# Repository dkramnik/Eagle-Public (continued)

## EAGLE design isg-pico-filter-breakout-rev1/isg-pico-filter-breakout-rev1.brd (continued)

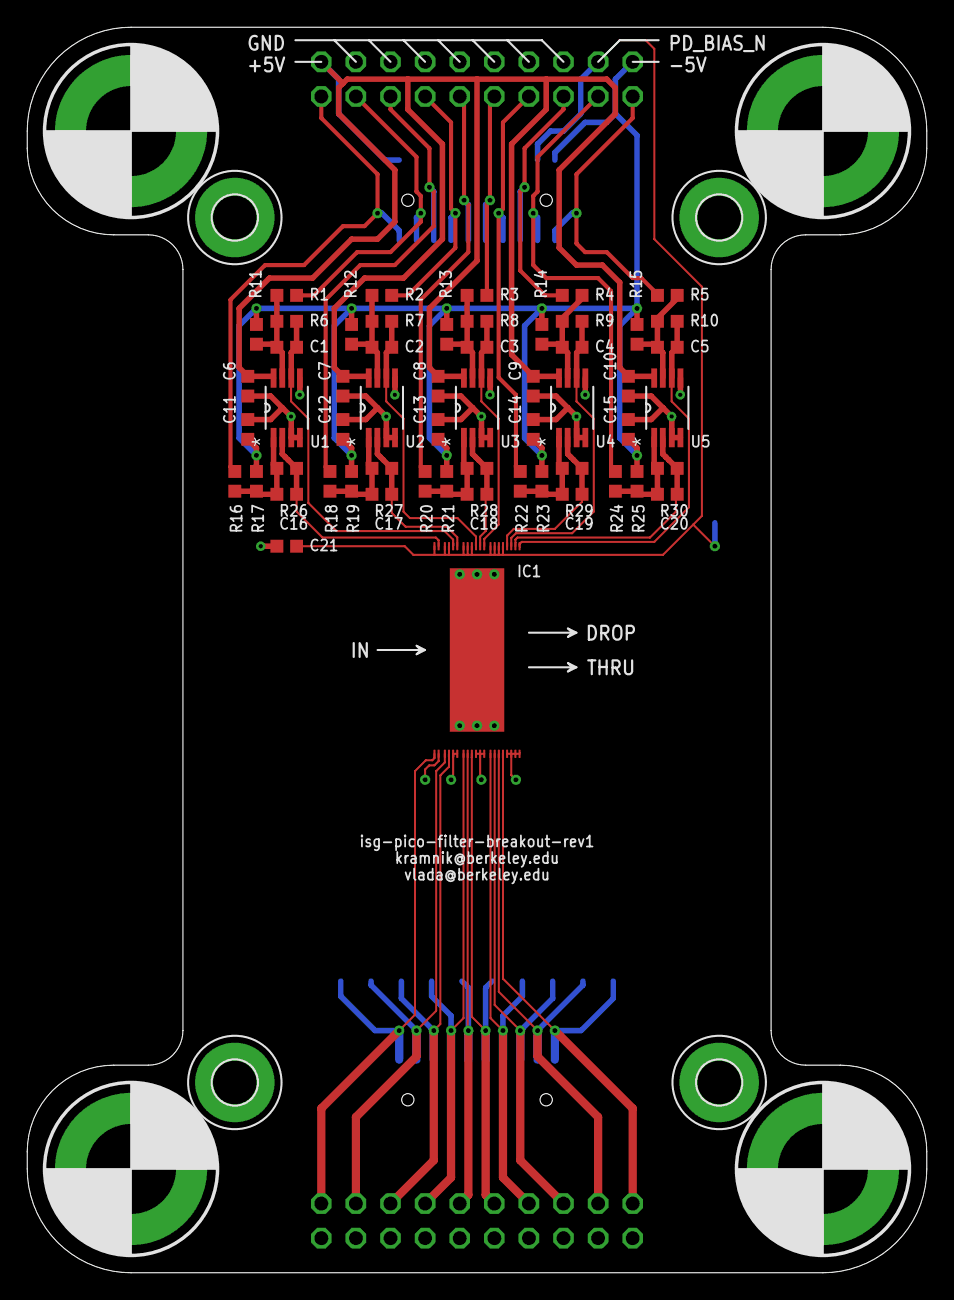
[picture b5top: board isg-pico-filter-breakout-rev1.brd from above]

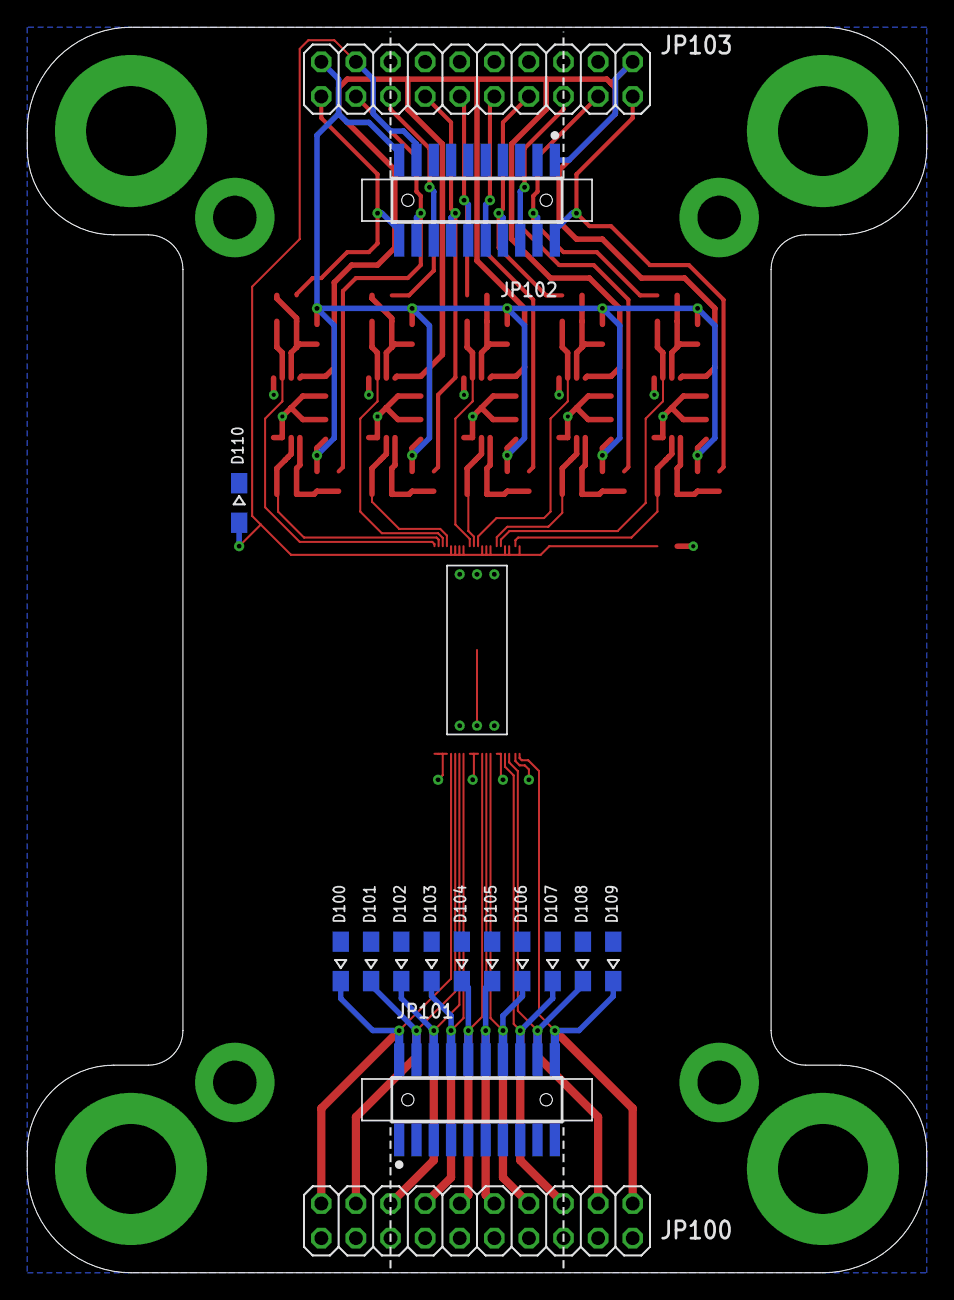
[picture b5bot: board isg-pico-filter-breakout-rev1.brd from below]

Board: 2 copper layers, 66.0 x 91.4 mm, 80 parts (15 on the bottom side), 44 nets.

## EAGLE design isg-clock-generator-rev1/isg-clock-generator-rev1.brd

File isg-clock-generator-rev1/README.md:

<h1>ISG Clock Generator Instructions:</h1>

This board is based off of the TI LMK03318EVM. Refer to the datasheet (http://www.ti.com/lit/ug/snau186/snau186.pdf) for detailed documentation and configuration instructions.

The LMK03318 has 4 on-chip memories: ROM, register file, SRAM, and EEPROM. The currently-used settings are stored in the register file, which is loaded either from ROM or EEPROM on startup, depending on the jumper configuration. The I2C interface writes only to the register file, which can then be transferred to the SRAM. The purpose of the (volatile) SRAM is to store data before it is written to EEPROM. The EEPROM can only be programmed from the contents of the SRAM. The various memory programming steps are separate actions with buttons located all over the TICS GUI, and multiple user actions need to be taken to successfully program the device. The TICS GUI also seems to be buggy, so be patient because it can take several attempts to get the PLL chip to output anything.

Important note: the on-chip EEPROM can only be reprogrammed 100 times, so be conservative when reconfiguring the clock source.

<h2>Required Rework</h2>

If assembled as specified in the BOM, the output coupling networks on channel 2 (the one with differential output) need to be reconfigured to work with the usual ISG CML2CMOS clock receiver design. Instead of DC coupling, each line should be AC-coupled and biased at around 0.8V. The required component changes are:

C34, C35 (AC-coupling) change from 0R 0402 jumper to 1nF 0402 RF capacitor
R22, R24 (pulldown to GND) change from DNP to 800R 0402
R23, R25 (pullup to VDDIO=1.8V) change from DNP to 1k 0402

Location of channel 2's output coupling network:

<h2>Jumper Configuration</h2>

Configure the jumpers like in the picture. STAT1 is on and STAT0 is off when the chip is working as desired.

<h2>Standard EEPROM Configuration Using TICS</h2>

todo

<h2>Custom EEPROM Configuration Using TICS</h2>

Step 1:

Before powering the PLL board, configure the jumpers and connect the TI USB2ANY adapter using the 10-pin ribbon cable.

Step 2:

Plug the TI USB2ANY in to the computer with a USB cable and launch the TICS Pro software. Make sure the adapter connects successfully. When first using the adapter, you will need to follow the on-screen instructions to update the firmware. To select the correct PLL chip, click "Select Device -> Clock Generator/Jitter Cleaner (Single Loop) -> LMK03318" in the main menu bar.

Step 3:

Power the PLL board using a 5V power supply. Hit the "Scan I2C Bus" button on the top-left side of the TICS Pro screen. If the PLL board is powered and connected correctly, the terminal in the bottom-left side of the screen will print: "A device responded at [addr]. Address will be updated."

Step 4:

Use pull-down menus under "Outputs" to configure the output driver type. Note that the configuration bits are written as soon as the menu item is clicked, you do not need to select the new settings and then separately hit a buttom to write to the PLL.

Step 5:

Go to "Wizard" and enter the desired frequencies on each output channel, then hit "Calculate" to populate the tables on the right side. With the tables populated, you can highlight one of the solutions and hit "Use Selected Sol" to program the PLL.

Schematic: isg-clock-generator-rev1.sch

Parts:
C1, C3, C10, C48: DNP; C0603
C2, C39, C41, C50, C52: CAP CER 0.1UF 25V X7R 0603 10%; C0603
C4, C11, C12, C18, C20, C23, C24, C26, C30, C36, C37: CAP CER 0.01uF X7R 0402; C0402
C5, C6, C8, C9, C14, C15, C16, C17, C19, C21, C22, C25, C27, C28, C29, C31, C32, C33, C38, C43, C44, C45, C47: CAP CER 0.1uF X7R 0402; C0402
C7, C46: 0R JUMPER 0603; C0603
C13, C34, C35: 0R JUMPER 0402; C0402
C40, C42: CAP CER 4.7UF 6.3V X5R 0603 10%; C0603
C49, C51: CAP CER 10000PF 25V X7R 0603 10%; C0603
C53: CAP CER 3300pF X7R 0603; C0603
C54: CAP CER 0.033uF X7R 0603; C0603
C55: CAP CER 22uF 6.3V 0603; C0603
C56, C57: CAP CER 1UF 10V X7R 0603 10%; C0603
C100, C101, C102, C103, C104, C105, C106, C107, C108, C109, C110, C111, C112: CAP CER 10uF 6.3V X5R 0603; C0603
D1, D2: SL23HE3_A/I; SMB
H1, H2, H3, H4: MOUNT-PAD-ROUND3.2; 3,2-PAD
IC1: LMK03318RHSR; RHS0048A_NV
IC2, IC3: TPS7A8001DRBR; DRB8_1P75X1P5
JP1: TI_USB2ANY; CON_OST_302-S101
JP2: STAT_LED_EN; JP1
JP3: GPIO0; JP2_ROUND
JP4: HWCTRL; JP2_ROUND
JP5: REFSEL; JP2_ROUND
JP6: EOS_MOTHERBOARD; JP5Q
JP7: PRIREF_VCM; JP2_ROUND
JP8: LOOP_FILTER; JP3Q
JP9: GPIO1; JP2_ROUND
JP10: GPIO2; JP2_ROUND
JP11: GPIO3; JP2_ROUND
JP12: GPIO4; JP2_ROUND
JP13: GPIO5; JP2_ROUND
JP14: XO_MARGIN; JP8Q
L1, L2, L3, L4, L5, L6, L7, L8, L9, L10: FERRITE BEAD 220 OHM 0402 1LN; R0402
LED1: STAT1=LO; CHIP-LED0805
LED2: STAT0=LO; CHIP-LED0805
Q1: 7M50072001; 3.2X2.5_KX-7
R1, R2: RES SMD 510 OHM 1% 1/10W 0603; R0603
R3, R7, R8, R9, R10, R11, R14, R18, R19, R36, R46, R54: DNP; R0603
R4, R12, R13: RES SMD 10K OHM 1% 1/10W 0603; R0603
R5, R37, R38, R39, R40, R41: RES SMD 1K OHM 1% 1/10W 0603; R0603
R6, R43, R44, R45: RES SMD 13.0K OHM 1% 1/10W 0603; R0603
R15, R16, R22, R23, R24, R25: DNP; R0402
R17, R20, R21: 0R JUMPER 0402; R0402
R26: RES SMD 3.92K OHM 1% 1/10W 0603; R0603
R27, R29, R31, R32, R33, R34, R35: RES SMD 4.99K OHM 1% 1/10W 0603; R0603
R28: RES SMD 1.62K OHM 1% 1/10W 0603; R0603
R30, R42: 0R JUMPER 0603; R0603
R47: RES SMD 0 OHM 1% 1/10W 0603; R0603
R48: RES SMD 2.32K OHM 1% 1/10W 0603; R0603
R49: RES SMD 5.62K OHM 1% 1/10W 0603; R0603
R50: RES SMD 10.5K OHM 1% 1/10W 0603; R0603
R51: RES SMD 18.7K OHM 1% 1/10W 0603; R0603
R52: RES SMD 34.8K OHM 1% 1/10W 0603; R0603
R53: RES SMD 84.5K OHM 1% 1/10W 0603; R0603
X1: OUT0_P; J502-ND-142-0701-881/886
X2: PRIREF_N; J502-ND-142-0701-881/886
X3: OUT2_P; J502-ND-142-0701-881/886
X4: PRIREF_P; J502-ND-142-0701-881/886
X5: OUT2_N; J502-ND-142-0701-881/886
X6: V_IN_EXT; 22-23-2021

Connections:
DECAP_DIG: C102.1, IC1.3 (CAP_DIG)
DECAP_LDO: C110.1, IC1.28 (CAP_LDO)
DECAP_PLL: C111.1, IC1.35 (CAP_PLL)
EXT_VDD: JP1.5, R3.1
GND: C1.2, C2.2, C3.2, C4.2, C5.2, C6.2, C8.2, C9.2, C10.2, C11.2, C12.2, C14.2, C15.2, C16.2, C17.2, C18.2, C19.2, C20.2, C21.2, C22.2, C23.2, C24.2, C25.2, C26.2, C27.2, C28.2, C29.2, C30.2, C31.2, C32.2, C33.2, C36.2, C37.2, C38.2, C39.2, C40.2, C41.2, C42.2, C43.2, C44.2, C45.2, C47.2, C48.2, C49.2, C50.2, C51.2, C52.2, C53.2, C54.2, C55.2, C56.2, C57.2, C100.2, C101.2, C102.2, C103.2, C104.2, C105.2, C106.2, C107.2, C108.2, C109.2, C110.2, C111.2, C112.2, H1.B3,2, H2.B3,2, H3.B3,2, H4.B3,2, IC1.49 (PAD), IC2.4 (GND), IC2.PAD (GND), IC2.PAD1 (GND), IC2.PAD2 (GND), IC2.PAD3 (GND), IC2.PAD4 (GND), IC2.VIA1 (GND), IC2.VIA2 (GND), IC3.4 (GND), IC3.PAD (GND), IC3.PAD1 (GND), IC3.PAD2 (GND), IC3.PAD3 (GND), IC3.PAD4 (GND), IC3.VIA1 (GND), IC3.VIA2 (GND), JP1.6, JP3.1, JP4.1, JP5.1, JP6.3, JP6.4, JP6.6, JP7.1, JP9.1, JP10.1, JP11.1, JP12.1, JP13.1, JP14.1, JP14.3, JP14.5, JP14.7, JP14.9, JP14.11, JP14.13, JP14.15, Q1.2 (GND), Q1.4 (GND), R9.1, R10.1, R16.1, R19.1, R22.1, R24.1, R26.2, R28.2, R33.1, R34.1, R35.1, R36.1, X1.G@1 (2), X1.G@2 (2), X1.G@3 (2), X1.G@4 (2), X2.G@1 (2), X2.G@2 (2), X2.G@3 (2), X2.G@4 (2), X3.G@1 (2), X3.G@2 (2), X3.G@3 (2), X3.G@4 (2), X4.G@1 (2), X4.G@2 (2), X4.G@3 (2), X4.G@4 (2), X5.G@1 (2), X5.G@2 (2), X5.G@3 (2), X5.G@4 (2), X6.1
GPIO0/SYNC: IC1.12 (GPIO0), JP1.1, R6.2
GPIO0_JUMPER: JP3.2, R6.1
GPIO1: IC1.24 (GPIO1), R33.2, R37.2, R43.1
GPIO1_JUMPER: JP9.2, R37.1
GPIO2: IC1.30 (GPIO2), R34.2, R38.2, R44.1
GPIO2_JUMPER: JP10.2, R38.1
GPIO3: IC1.31 (GPIO3), R35.2, R39.2, R45.1
GPIO3_JUMPER: JP11.2, R39.1
GPIO4: IC1.32 (GPIO4), R36.2, R40.2, R46.1
GPIO4_JUMPER: JP12.2, R40.1
GPIO5: IC1.33 (GPIO5), R42.1
GPIO5_JUMPER: JP13.2, R42.2, R47.1, R48.1, R49.1, R50.1, R51.1, R52.1, R53.1, R54.1
GPIO5_SEL_1_2: JP14.2, R47.2
GPIO5_SEL_3_4: JP14.4, R48.2
GPIO5_SEL_5_6: JP14.6, R49.2
GPIO5_SEL_7_8: JP14.8, R50.2
GPIO5_SEL_9_10: JP14.10, R51.2
GPIO5_SEL_11_12: JP14.12, R52.2
GPIO5_SEL_13_14: JP14.14, R53.2
GPIO5_SEL_15_16: JP14.16, R54.2
HWCTRL_JUMPER: JP4.2, R4.1
HW_SW_CTRL: IC1.9 (HW_SW_CTRL), JP1.3, JP6.8, R4.2, R7.1, R9.2
LDO_PVCORE_EN: IC3.5 (EN), R32.2
LDO_PVCORE_FB: IC3.3 (FB/SNS), R28.1, R29.1
LDO_PVCORE_SS: C51.1, IC3.6 (NR/SS)
LDO_PVDDIO_EN: IC2.5 (EN), R31.2
LDO_PVDDIO_FB: IC2.3 (FB/SNS), R26.1, R27.1
LDO_PVDDIO_SS: C49.1, IC2.6 (NR/SS)
LF1: C48.1, IC1.34 (LF), R30.1
LF_FRAC_N: C54.1, JP8.3
LF_INT_N\: C53.1, JP8.1
LF_NARROW: C55.1, JP8.5
LF_R: JP8.2, JP8.4, JP8.6, R30.2
unnamed: LED1.A, R1.1
unnamed: LED2.A, R2.1
NC_OUT0_N: IC1.15 (OUT0_N)
NC_OUT1_N: IC1.16 (OUT1_N)
NC_OUT1_P: IC1.17 (OUT1_P)
NC_OUT3_N: IC1.22 (OUT3_N)
NC_OUT3_P: IC1.23 (OUT3_P)
NC_OUT4_N: IC1.38 (OUT4_N)
NC_OUT4_P: IC1.39 (OUT4_P)
NC_OUT5_N: IC1.41 (OUT5_N)
NC_OUT5_P: IC1.42 (OUT5_P)
NC_OUT6_N: IC1.44 (OUT6_N)
NC_OUT6_P: IC1.45 (OUT6_P)
NC_OUT7_N: IC1.47 (OUT7_N)
NC_OUT7_P: IC1.48 (OUT7_P)
NC_PIN: IC1.29 (NC)
NC_USB2ANY_CONN_1: JP1.7
NC_USB2ANY_CONN_2: JP1.8
OUT0_P: IC1.14 (OUT0_P), R17.2
OUT0_R_C_P: C13.2, R15.1, R16.2, X1.1
OUT0_R_P: C13.1, R17.1
OUT2_N: IC1.21 (OUT2_N), R21.2
OUT2_P: IC1.20 (OUT2_P), R20.2
OUT2_R_C_N: C35.2, R24.2, R25.1, X5.1
OUT2_R_C_P: C34.2, R22.2, R23.1, X3.1
OUT2_R_N: C35.1, R21.1
OUT2_R_P: C34.1, R20.1
PDN: C4.1, IC1.13 (PDN), JP1.2
PP_P1V8_VDDO: C14.1, C15.1, C19.1, C22.1, C25.1, C29.1, C32.1, C33.1, C39.1, C40.1, C45.1, IC2.1 (OUT_2), IC2.2 (OUT), L3.2, L4.2, L5.2, L6.2, L7.2, L8.2, R15.2, R23.2, R25.2, R27.2
PP_P3V3_PLL_CORE: C2.1, C5.1, C6.1, C41.1, C42.1, C43.1, C47.1, IC3.1 (OUT_2), IC3.2 (OUT), JP2.2, JP3.3, JP4.3, JP5.3, JP9.3, JP10.3, JP11.3, JP12.3, L1.1, L2.1, L9.1, L10.1, R3.2, R7.2, R8.2, R12.2, R13.2, R18.2, R29.2, R31.1, R41.2, R43.2, R44.2, R45.2, R46.2
PRIREF_N: C7.2, IC1.7 (PRIREF_N), R11.2
PRIREF_P: C46.2, IC1.6 (PRIREF_P), R14.2
PRIREF_R_N: C7.1, X2.1
PRIREF_R_P: C46.1, X4.1
PRIREF_VCM: C1.1, JP7.2, R11.1, R14.1
PRIREF_VCM_DIVIDER: JP7.3, R18.1, R19.2
PULLUP_GPIO5: JP13.3, R41.1
REFSEL: IC1.8 (REFSEL), JP1.4, R5.2, R8.1, R10.2
REFSEL_JUMPER: JP5.2, R5.1
SCL: IC1.26 (SCL), JP1.9, JP6.10, R13.1
SDA: IC1.25 (SDA), JP1.10, JP6.9, R12.1
SECREF_N: C10.1, IC1.11 (SECREF_N), Q1.1
SECREF_P: C3.1, IC1.10 (SECREF_P), Q1.3 (2)
STATUS0: IC1.1 (STATUS0), JP6.7, LED2.C
STATUS1: IC1.2 (STATUS1), JP6.5, LED1.C
STATUS_LED_PWR: JP2.1, R1.2, R2.2
VDDO_01: C16.1, C20.1, C104.1, IC1.18 (VDDO_01), L4.1
VDDO_4: C30.1, C31.1, C108.1, IC1.37 (VDDO_4), L8.1
VDDO_5: C26.1, C28.1, C107.1, IC1.40 (VDDO_5), L7.1
VDDO_6: C21.1, C23.1, C105.1, IC1.43 (VDDO_6), L5.1
VDDO_7: C17.1, C18.1, C103.1, IC1.46 (VDDO_7), L3.1
VDDO_23: C24.1, C27.1, C106.1, IC1.19 (VDDO_23), L6.1
VDD_DIG: C9.1, C12.1, C101.1, IC1.4 (VDD_DIG), L2.2
VDD_IN: C8.1, C11.1, C100.1, IC1.5 (VDD_IN), L1.2
VDD_LDO: C36.1, C44.1, C109.1, IC1.27 (VDD_LDO), L10.2
VDD_PLL: C37.1, C38.1, C112.1, IC1.36 (VDD_PLL), L9.2
VIN: C50.1, C52.1, C56.1, C57.1, D1.C, D2.C, IC2.7 (IN_2), IC2.8 (IN), IC3.7 (IN_2), IC3.8 (IN), R32.1
VIN_EXT: D2.A, X6.2
VIN_MLB: D1.A, JP6.1, JP6.2

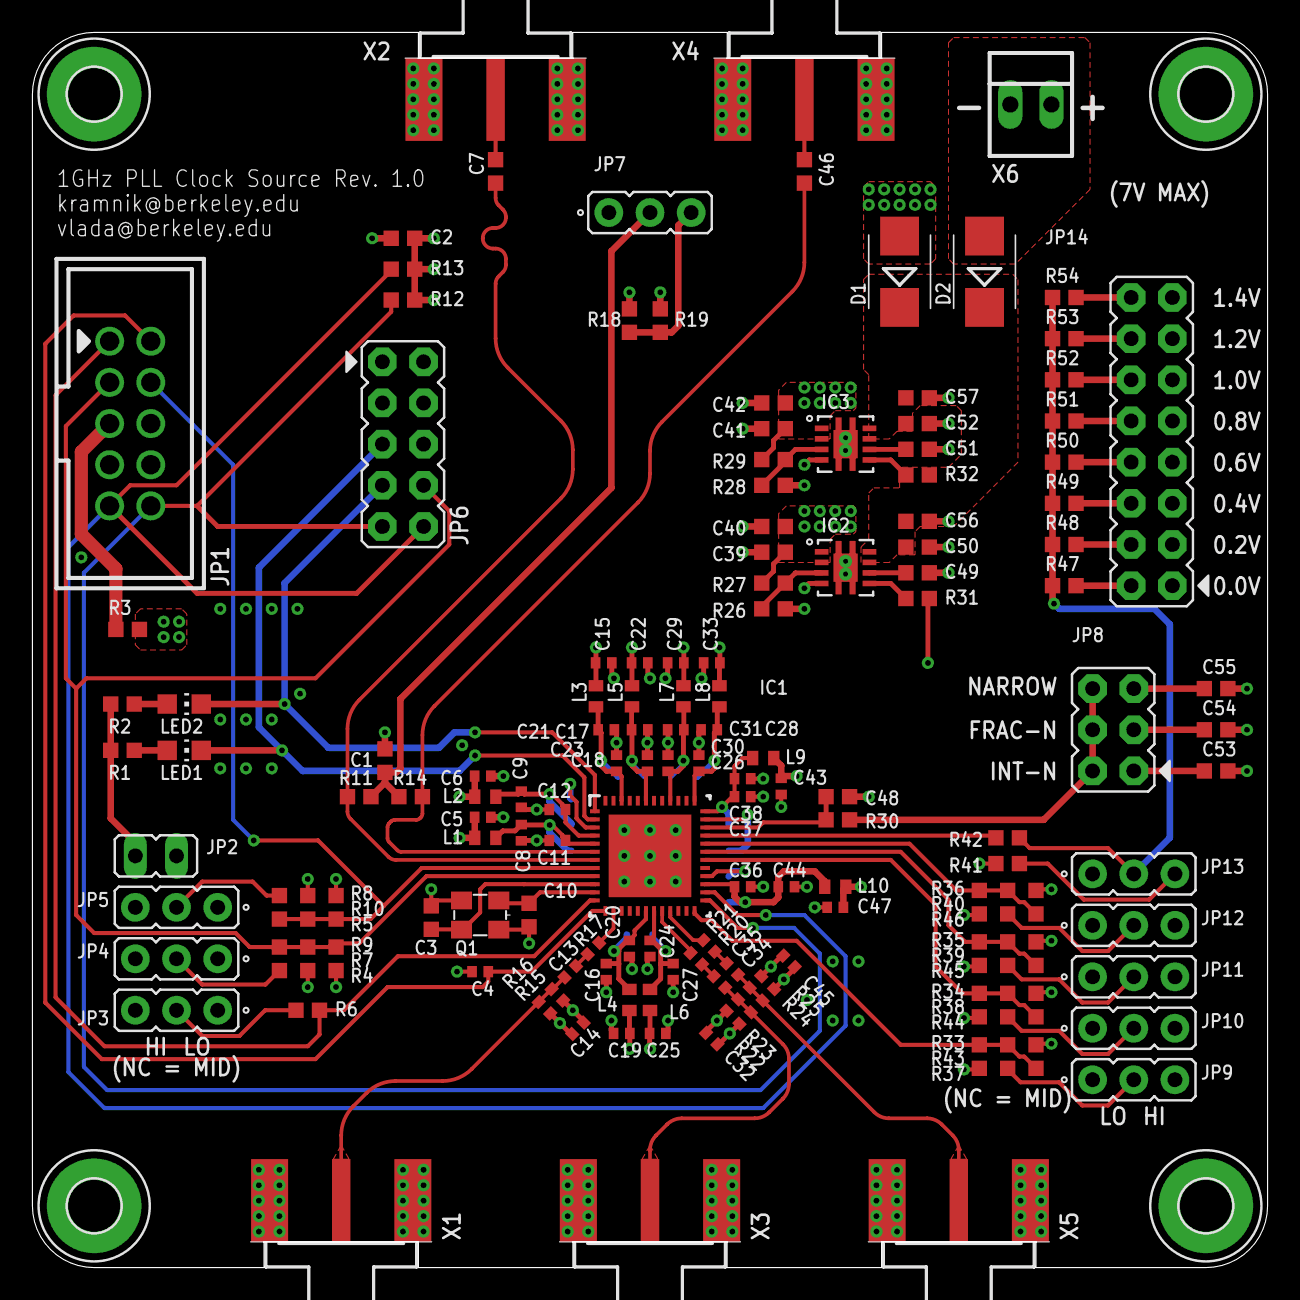
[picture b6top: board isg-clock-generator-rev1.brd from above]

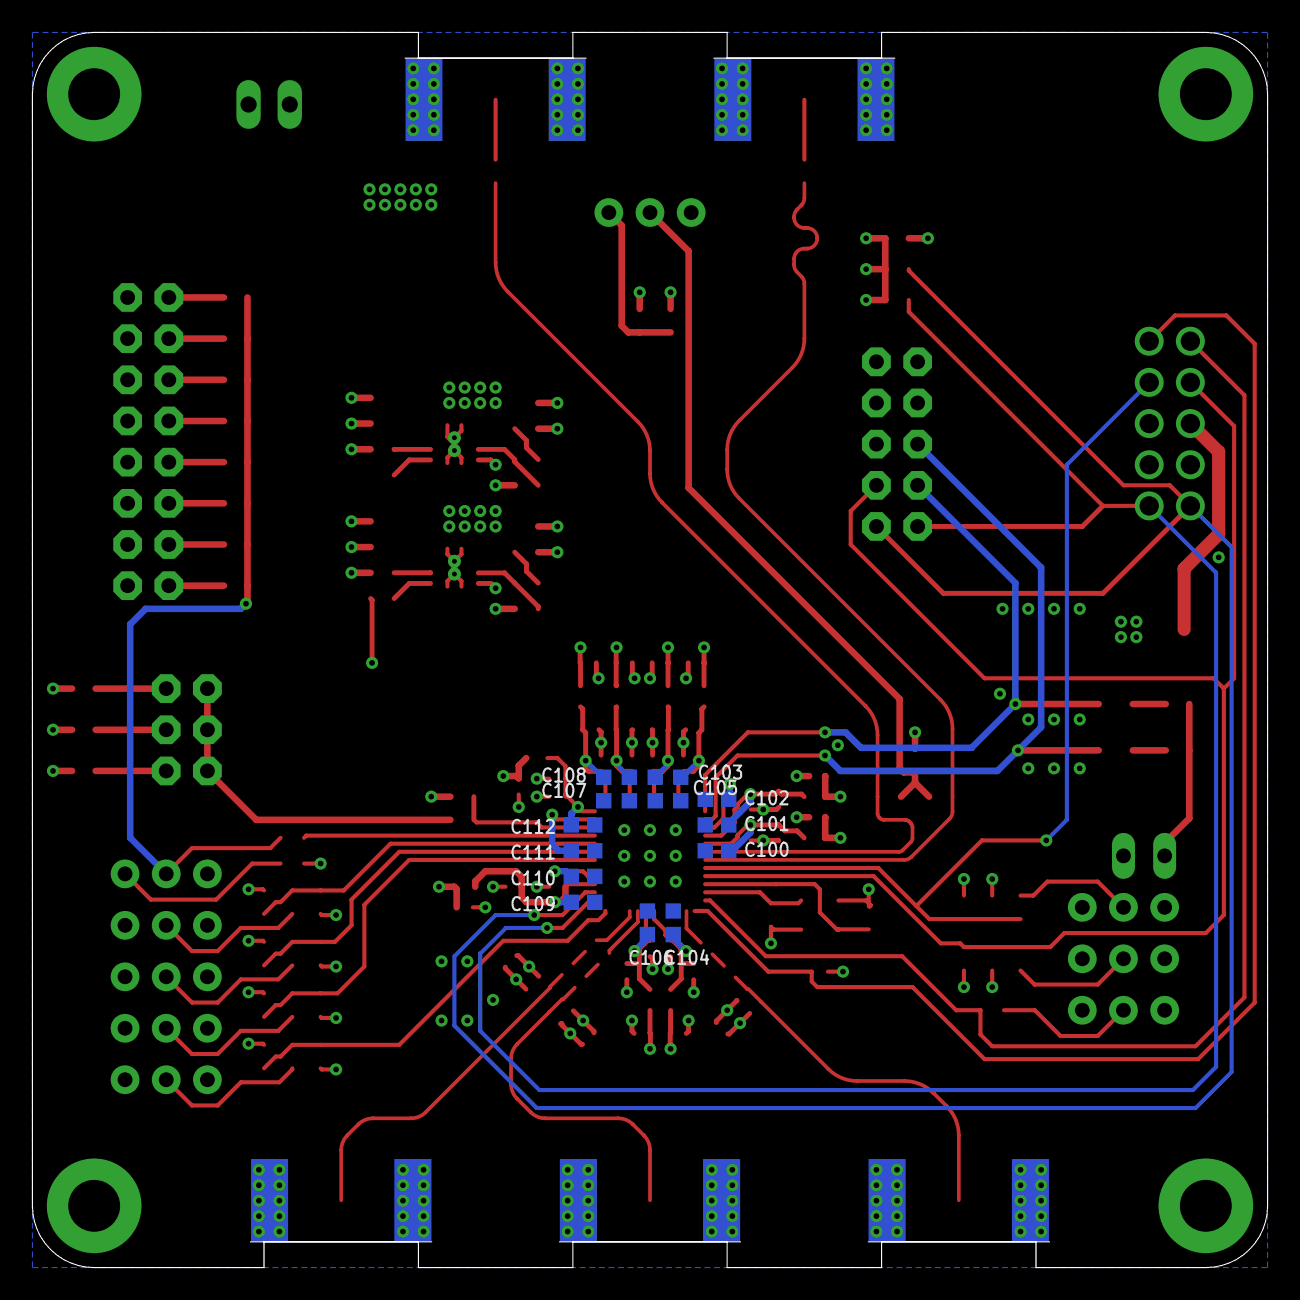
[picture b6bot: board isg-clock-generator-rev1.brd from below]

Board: 4 copper layers, 76.2 x 76.2 mm, 166 parts (13 on the bottom side), 81 nets.

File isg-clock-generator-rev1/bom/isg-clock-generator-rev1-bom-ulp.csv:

"Qty";"Value";"Device";"Package";"Parts";"Description";"MF";"MPN";"OC_FARNELL";"OC_NEWARK";"VALUE";
"2";"0R JUMPER";"C-EUC0603";"C0603";"C7, C46";"CAPACITOR, European symbol";"";"";"";"";"";
"3";"0R JUMPER 0402";"C-EUC0402";"C0402";"C13, C34, C35";"CAPACITOR, European symbol";"";"";"";"";"";
"3";"0R JUMPER 0402";"R-EU_R0402";"R0402";"R17, R20, R21";"RESISTOR, European symbol";"";"";"";"";"";
"2";"0R JUMPER 0603";"R-EU_R0603";"R0603";"R30, R42";"RESISTOR, European symbol";"";"";"";"";"";
"1";"7M50072001";"KX-7";"3.2X2.5_KX-7";"Q1";"Quartz Crystals (MHz) SMD:";"";"";"";"";"";
"11";"CAP CER 0.01uF X7R 0402";"C-EUC0402";"C0402";"C4, C11, C12, C18, C20, C23, C24, C26, C30, C36, C37";"CAPACITOR, European symbol";"";"";"";"";"";
"1";"CAP CER 0.033uF 0603";"C-EUC0603";"C0603";"C54";"CAPACITOR, European symbol";"";"";"";"";"";
"5";"CAP CER 0.1UF 25V X7R 0603 10%";"C-EUC0603";"C0603";"C2, C39, C41, C50, C52";"CAPACITOR, European symbol";"";"";"";"";"";
"23";"CAP CER 0.1uF X7R 0402";"C-EUC0402";"C0402";"C5, C6, C8, C9, C14, C15, C16, C17, C19, C21, C22, C25, C27, C28, C29, C31, C32, C33, C38, C43, C44, C45, C47";"CAPACITOR, European symbol";"";"";"";"";"";
"2";"CAP CER 10000PF 25V X7R 0603 10%";"C-EUC0603";"C0603";"C49, C51";"CAPACITOR, European symbol";"";"";"";"";"";
"13";"CAP CER 10uF 6.3V X5R 0603";"C-EUC0603";"C0603";"C100, C101, C102, C103, C104, C105, C106, C107, C108, C109, C110, C111, C112";"CAPACITOR, European symbol";"";"";"";"";"";
"1";"CAP CER 22uF 6.3V 0603";"C-EUC0603";"C0603";"C55";"CAPACITOR, European symbol";"";"";"";"";"";
"1";"CAP CER 3300pF 0603";"C-EUC0603";"C0603";"C53";"CAPACITOR, European symbol";"";"";"";"";"";
"2";"CAP CER 4.7UF 6.3V X5R 0603 10%";"C-EUC0603";"C0603";"C40, C42";"CAPACITOR, European symbol";"";"";"";"";"";
"3";"DNP";"C-EUC0603";"C0603";"C3, C10, C48";"CAPACITOR, European symbol";"";"";"";"";"";
"6";"DNP";"R-EU_R0402";"R0402";"R15, R16, R22, R23, R24, R25";"RESISTOR, European symbol";"";"";"";"";"";
"10";"DNP";"R-EU_R0603";"R0603";"R3, R7, R8, R9, R10, R11, R14, R36, R46, R54";"RESISTOR, European symbol";"";"";"";"";"";
"1";"DNP 0603";"C-EUC0603";"C0603";"C1";"CAPACITOR, European symbol";"";"";"";"";"";
"2";"DNP 0603";"R-EU_R0603";"R0603";"R18, R19";"RESISTOR, European symbol";"";"";"";"";"";
"1";"EOS_MOTHERBOARD";"JP5Q";"JP5Q";"JP6";"JUMPER";"";"";"";"";"";
"10";"FERRITE BEAD 220 OHM 0402 1LN";"INDUCTOR0402";"R0402";"L1, L2, L3, L4, L5, L6, L7, L8, L9, L10";"";"";"";"";"";"";
"1";"GPIO0";"JP2E";"JP2_ROUND";"JP3";"JUMPER";"";"";"";"";"";
"1";"GPIO1";"JP2E";"JP2_ROUND";"JP9";"JUMPER";"";"";"";"";"";
"1";"GPIO2";"JP2E";"JP2_ROUND";"JP10";"JUMPER";"";"";"";"";"";
"1";"GPIO3";"JP2E";"JP2_ROUND";"JP11";"JUMPER";"";"";"";"";"";
"1";"GPIO4";"JP2E";"JP2_ROUND";"JP12";"JUMPER";"";"";"";"";"";
"1";"GPIO5";"JP2E";"JP2_ROUND";"JP13";"JUMPER";"";"";"";"";"";
"1";"HWCTRL";"JP2E";"JP2_ROUND";"JP4";"JUMPER";"";"";"";"";"";
"1";"LMK03318RHSR";"LMK03318RHSRRHS0048A_NV";"RHS0048A_NV";"IC1";"";"";"";"";"";"LMK03318RHSR";
"1";"LOOP_FILTER";"JP3Q";"JP3Q";"JP8";"JUMPER";"";"";"";"";"";
"4";"MOUNT-PAD-ROUND3.2";"MOUNT-PAD-ROUND3.2";"3,2-PAD";"H1, H2, H3, H4";"MOUNTING PAD, round";"";"";"";"";"";
"1";"OUT0_P";"SMA-142-0701-881/886";"J502-ND-142-0701-881/886";"X1";"SMA 50 Ohm End Launch Jack Receptacle - Round Contact";"JOHNSON COMPONENTS";"142-0701-881";"1608603";"08B906";"";
"1";"OUT2_N";"SMA-142-0701-881/886";"J502-ND-142-0701-881/886";"X5";"SMA 50 Ohm End Launch Jack Receptacle - Round Contact";"JOHNSON COMPONENTS";"142-0701-881";"1608603";"08B906";"";
"1";"OUT2_P";"SMA-142-0701-881/886";"J502-ND-142-0701-881/886";"X3";"SMA 50 Ohm End Launch Jack Receptacle - Round Contact";"JOHNSON COMPONENTS";"142-0701-881";"1608603";"08B906";"";
"1";"PRIREF_N";"SMA-142-0701-881/886";"J502-ND-142-0701-881/886";"X2";"SMA 50 Ohm End Launch Jack Receptacle - Round Contact";"JOHNSON COMPONENTS";"142-0701-881";"1608603";"08B906";"";
"1";"PRIREF_P";"SMA-142-0701-881/886";"J502-ND-142-0701-881/886";"X4";"SMA 50 Ohm End Launch Jack Receptacle - Round Contact";"JOHNSON COMPONENTS";"142-0701-881";"1608603";"08B906";"";
"1";"PRIREF_VCM";"JP2E";"JP2_ROUND";"JP7";"JUMPER";"";"";"";"";"";
"1";"REFSEL";"JP2E";"JP2_ROUND";"JP5";"JUMPER";"";"";"";"";"";
"1";"RES SMD 0 OHM 1% 1/10W 0603";"R-EU_R0603";"R0603";"R47";"RESISTOR, European symbol";"";"";"";"";"";
"1";"RES SMD 1.62K OHM 1% 1/10W 0603";"R-EU_R0603";"R0603";"R28";"RESISTOR, European symbol";"";"";"";"";"";
"1";"RES SMD 10.5K OHM 1% 1/10W 0603";"R-EU_R0603";"R0603";"R50";"RESISTOR, European symbol";"";"";"";"";"";
"3";"RES SMD 10K OHM 1% 1/10W 0603";"R-EU_R0603";"R0603";"R4, R12, R13";"RESISTOR, European symbol";"";"";"";"";"";
"4";"RES SMD 13.0K OHM 1% 1/10W 0603";"R-EU_R0603";"R0603";"R6, R43, R44, R45";"RESISTOR, European symbol";"";"";"";"";"";
"1";"RES SMD 18.7K OHM 1% 1/10W 0603";"R-EU_R0603";"R0603";"R51";"RESISTOR, European symbol";"";"";"";"";"";
"6";"RES SMD 1K OHM 1% 1/10W 0603";"R-EU_R0603";"R0603";"R5, R37, R38, R39, R40, R41";"RESISTOR, European symbol";"";"";"";"";"";
"1";"RES SMD 2.32K OHM 1% 1/10W 0603";"R-EU_R0603";"R0603";"R48";"RESISTOR, European symbol";"";"";"";"";"";
"1";"RES SMD 3.92K OHM 1% 1/10W 0603";"R-EU_R0603";"R0603";"R26";"RESISTOR, European symbol";"";"";"";"";"";
"1";"RES SMD 34.8K OHM 1% 1/10W 0603";"R-EU_R0603";"R0603";"R52";"RESISTOR, European symbol";"";"";"";"";"";
"7";"RES SMD 4.99K OHM 1% 1/10W 0603";"R-EU_R0603";"R0603";"R27, R29, R31, R32, R33, R34, R35";"RESISTOR, European symbol";"";"";"";"";"";
"1";"RES SMD 5.62K OHM 1% 1/10W 0603";"R-EU_R0603";"R0603";"R49";"RESISTOR, European symbol";"";"";"";"";"";
"2";"RES SMD 510R 0603";"R-EU_R0603";"R0603";"R1, R2";"RESISTOR, European symbol";"";"";"";"";"";
"1";"RES SMD 84.5K OHM 1% 1/10W 0603";"R-EU_R0603";"R0603";"R53";"RESISTOR, European symbol";"";"";"";"";"";
"2";"SL23HE3_A/I";"SCHOTTKY-DIODESMD";"SMB";"D1, D2";"Schottky Diode";"";"";"";"";"";
"1";"STAT0=LO";"LEDCHIP-LED0805";"CHIP-LED0805";"LED2";"LED";"";"";"";"";"";
"1";"STAT1=LO";"LEDCHIP-LED0805";"CHIP-LED0805";"LED1";"LED";"";"";"";"";"";
"1";"STAT_LED_EN";"JP1Q";"JP1";"JP2";"JUMPER";"";"";"";"";"";
"1";"TI_USB2ANY";"CON_OST_302-S101";"CON_OST_302-S101";"JP1";"";"";"";"";"";"";
"2";"TPS7A8001DRBR";"TPS7A8001DRBR";"DRB8_1P75X1P5";"IC2, IC3";"";"";"";"";"";"TPS7A8001DRBR";
"1";"V_IN_EXT";"22-23-2021";"22-23-2021";"X6";".100" (2.54mm) Center Header - 2 Pin";"MOLEX";"22-23-2021";"1462926";"25C3832";"";
"1";"XO_MARGIN";"JP8Q";"JP8Q";"JP14";"JUMPER";"";"";"";"";"";

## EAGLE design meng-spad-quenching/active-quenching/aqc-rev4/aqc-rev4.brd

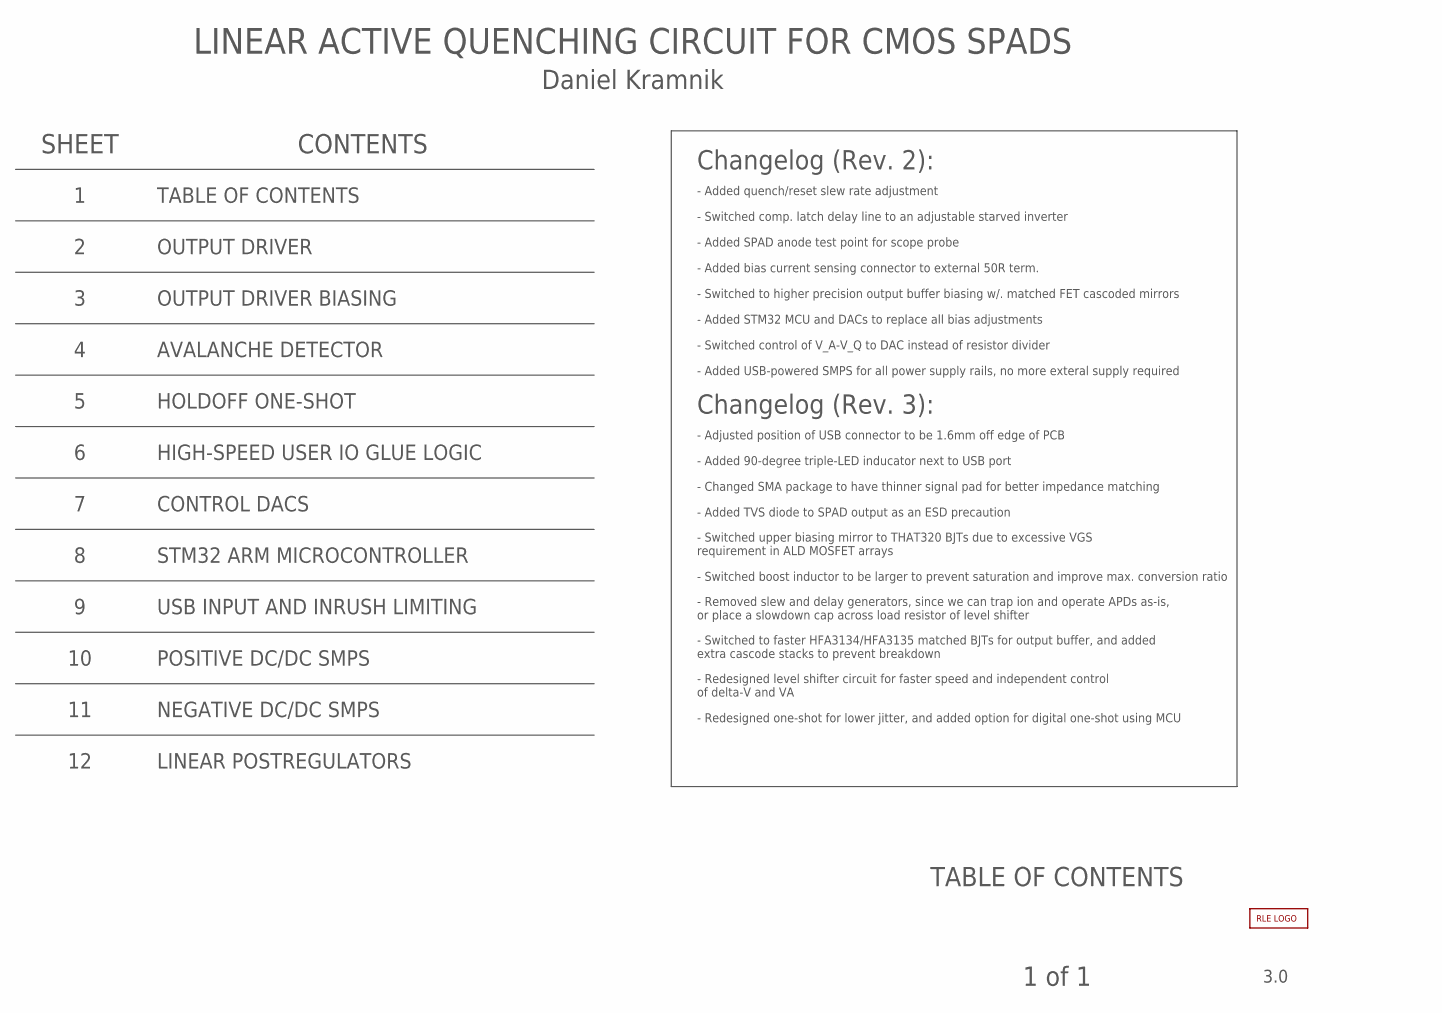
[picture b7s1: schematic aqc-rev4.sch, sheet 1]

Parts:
DNP1000: RLE_LOGO

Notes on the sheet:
Changelog (Rev. 2):
- Added quench/reset slew rate adjustment
- Switched comp. latch delay line to an adjustable starved inverter
- Added SPAD anode test point for scope probe
- Added bias current sensing connector to external 50R term.
- Added USB-powered SMPS for all power supply rails, no more exteral supply required
- Added STM32 MCU and DACs to replace all bias adjustments
- Switched to higher precision output buffer biasing w/. matched FET cascoded mirrors
- Switched control of V_A-V_Q to DAC instead of resistor divider
TABLE OF CONTENTS
3.0
1 of 1
LINEAR ACTIVE QUENCHING CIRCUIT FOR CMOS SPADS
SHEET
CONTENTS
Daniel Kramnik
OUTPUT DRIVER
OUTPUT DRIVER BIASING
STM32 ARM MICROCONTROLLER
CONTROL DACS
AVALANCHE DETECTOR
POSITIVE DC/DC SMPS
NEGATIVE DC/DC SMPS
USB INPUT AND INRUSH LIMITING
HOLDOFF ONE-SHOT
LINEAR POSTREGULATORS
Changelog (Rev. 3):
- Adjusted position of USB connector to be 1.6mm off edge of PCB
- Added 90-degree triple-LED inducator next to USB port
- Changed SMA package to have thinner signal pad for better impedance matching
- Added TVS diode to SPAD output as an ESD precaution
- Switched upper biasing mirror to THAT320 BJTs due to excessive VGS requirement in ALD MOSFET arrays
- Switched boost inductor to be larger to prevent saturation and improve max. conversion ratio
- Removed slew and delay generators, since we can trap ion and operate APDs as-is, or place a slowdown cap across load resistor of level shifter
- Switched to faster HFA3134/HFA3135 matched BJTs for output buffer, and added extra cascode stacks to prevent breakdown
- Redesigned level shifter circuit for faster speed and independent control of delta-V and VA
- Redesigned one-shot for lower jitter, and added option for digital one-shot using MCU
HIGH-SPEED USER IO GLUE LOGIC

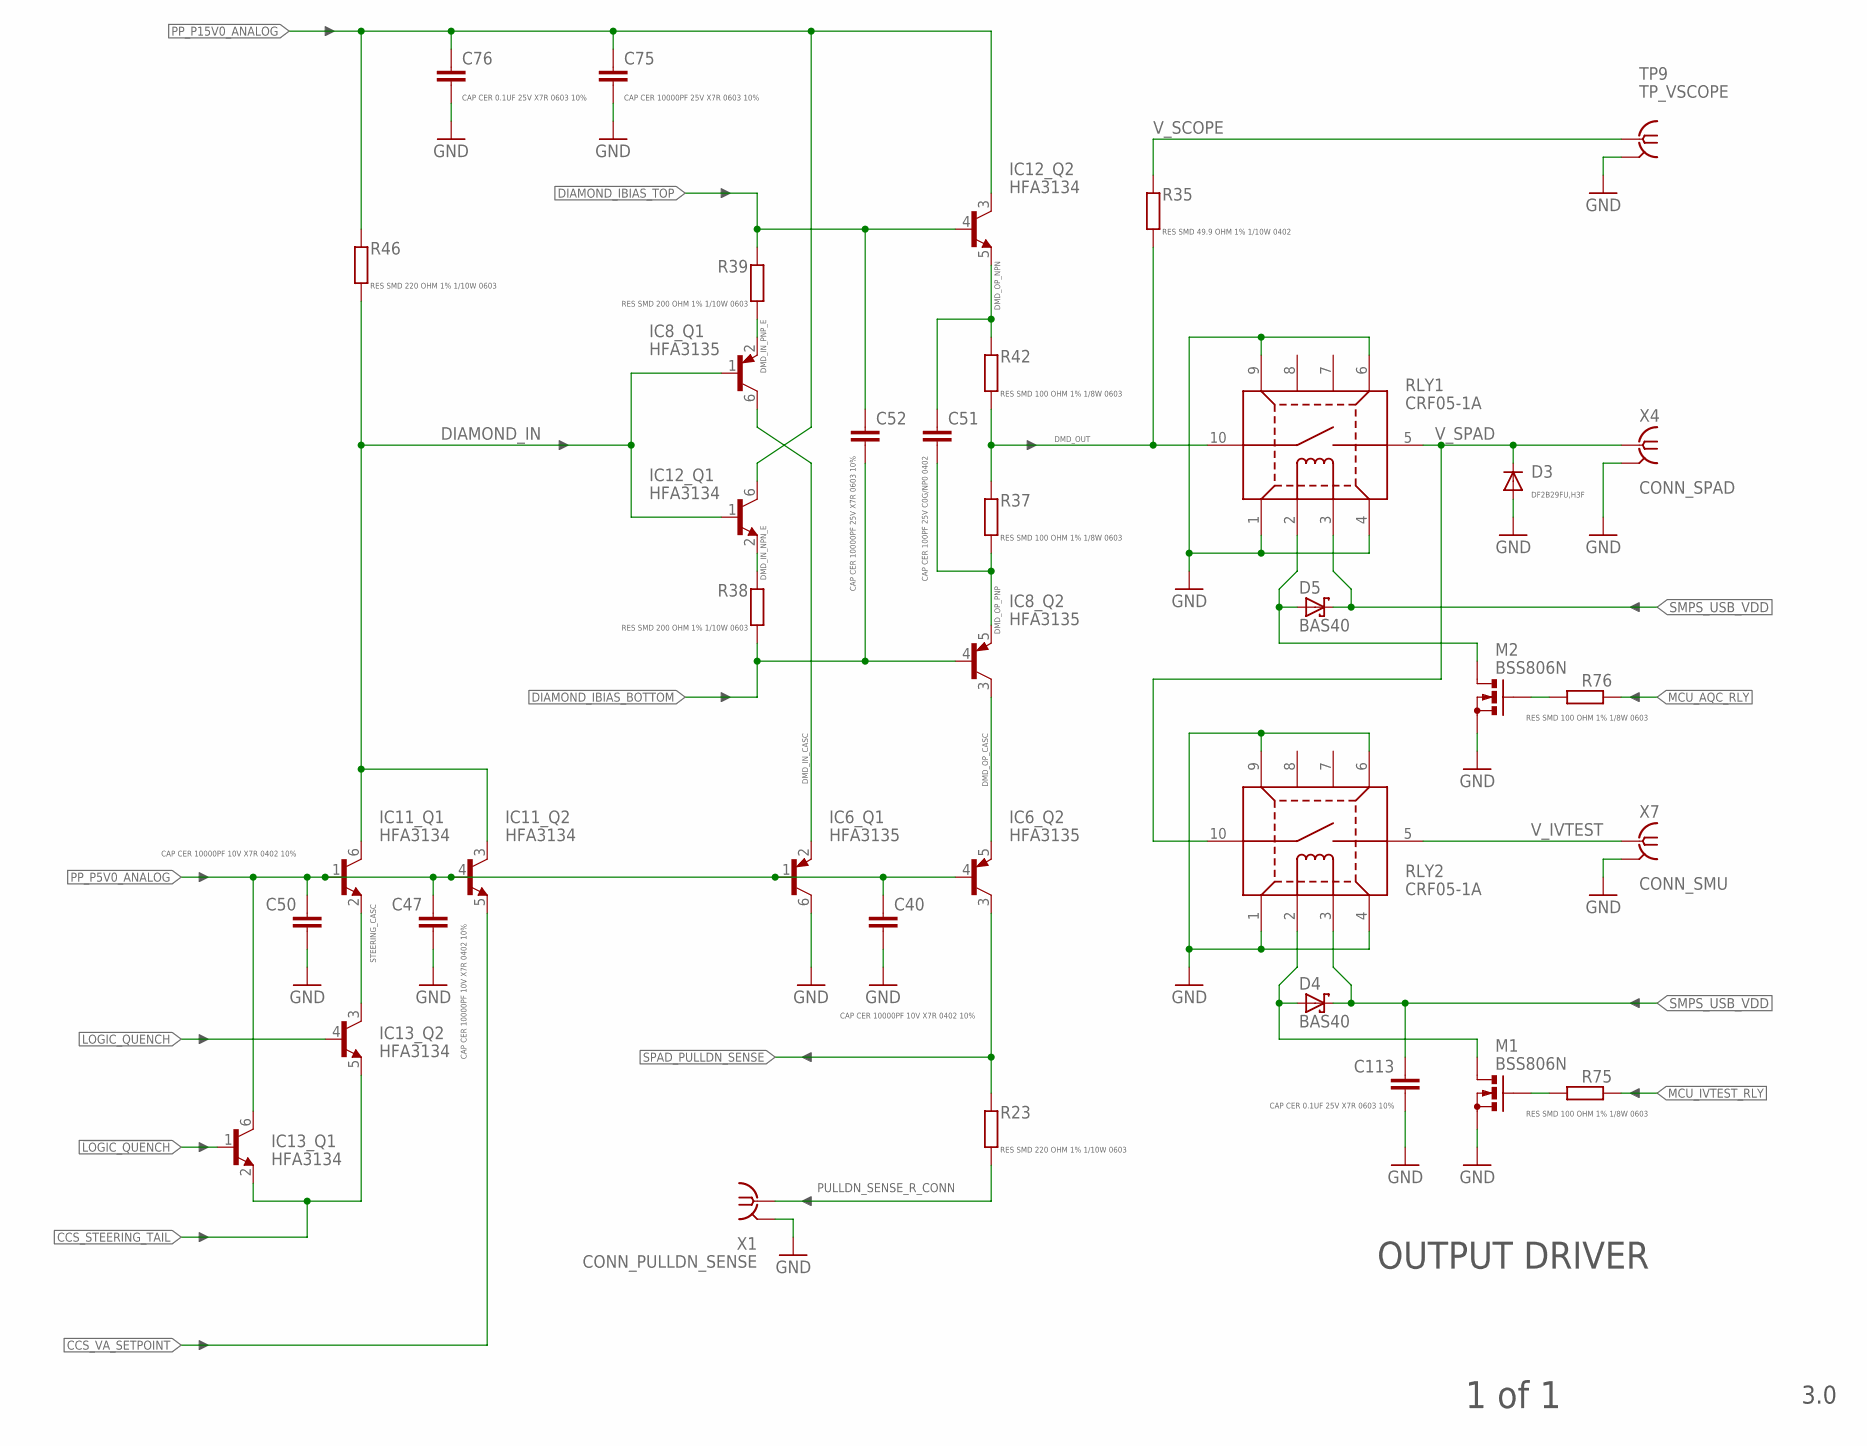
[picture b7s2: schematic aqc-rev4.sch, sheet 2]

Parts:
C40, C47, C50: CAP CER 10000PF 10V X7R 0402 10%; C0402
C51: CAP CER 100PF 25V C0G/NP0 0402; C0402
C52, C75: CAP CER 10000PF 25V X7R 0603 10%; C0603
C76, C113: CAP CER 0.1UF 25V X7R 0603 10%; C0603
D3: DF2B29FU,H3F; SOD523
D4, D5: BAS40; SOT23
IC6, IC8: HFA3135; SOT23-6L
IC11, IC12, IC13: HFA3134; SOT23-6L
M1, M2: BSS806N; SOT23R_INFINEON
R23, R46: RES SMD 220 OHM 1% 1/10W 0603; R0603
R35: RES SMD 49.9 OHM 1% 1/10W 0402; R0402
R37, R42, R75, R76: RES SMD 100 OHM 1% 1/8W 0603; R0603
R38, R39: RES SMD 200 OHM 1% 1/10W 0603; R0603
RLY1, RLY2: CRF05-1A; MEDER_RELAY_CRF
TP9: TP_VSCOPE; JOHNSON-129-0701-30X
X1: CONN_PULLDN_SENSE; J502-ND-142-0701-881/886; MPN 142-0711-871
X4: CONN_SPAD; J502-ND-142-0701-881/886
X7: CONN_SMU; J502-ND-142-0701-881/886

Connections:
!LOGIC_QUENCH: IC13.1 (B); also elsewhere on the board
CCS_STEERING_TAIL: IC13.2 (E), IC13.5 (E); also elsewhere on the board
CCS_VA_SETPOINT: IC11.5 (E); also elsewhere on the board
DIAMOND_IBIAS_BOTTOM: C52.2, IC8.4 (B), R38.1; also elsewhere on the board
DIAMOND_IBIAS_TOP: C52.1, IC12.4 (B), R39.2; also elsewhere on the board
DIAMOND_IN: IC8.1 (B), IC11.3 (C), IC11.6 (C), IC12.1 (B), R46.1
DMD_IN_CASC: IC6.2 (E), IC8.6 (C)
DMD_IN_NPN_E: IC12.2 (E), R38.2
DMD_IN_PNP_E: IC8.2 (E), R39.1
DMD_OP_CASC: IC6.5 (E), IC8.3 (C)
DMD_OP_NPN: C51.1, IC12.5 (E), R42.2
DMD_OP_PNP: C51.2, IC8.5 (E), R37.1
DMD_OUT: R35.1, R37.2, R42.1, RLY1.10 (PIN10)
GND: C40.2, C47.2, C50.2, C75.2, C76.2, C113.2, D3.A, IC6.6 (C), M1.2 (S), M2.2 (S), RLY1.1 (PIN1), RLY1.4 (PIN4), RLY1.6 (PIN6), RLY1.9 (PIN9), RLY2.1 (PIN1), RLY2.4 (PIN4), RLY2.6 (PIN6), RLY2.9 (PIN9), TP9.GND1 (GND), TP9.GND2 (GND), X1.G@1 (GND), X1.G@2 (GND), X1.G@3 (GND), X1.G@4 (GND), X4.G@1 (GND), X4.G@2 (GND), X4.G@3 (GND), X4.G@4 (GND), X7.G@1 (GND), X7.G@2 (GND), X7.G@3 (GND), X7.G@4 (GND); also elsewhere on the board
LOGIC_QUENCH: IC13.4 (B); also elsewhere on the board
MCU_AQC_RLY: R76.2; also elsewhere on the board
MCU_IVTEST_RLY: R75.2; also elsewhere on the board
unnamed: M2.1 (G), R76.1
unnamed: D5.1 (A), M2.3 (D), RLY1.2 (PIN2)
unnamed: D4.1 (A), M1.3 (D), RLY2.2 (PIN2)
unnamed: M1.1 (G), R75.1
PP_P5V0_ANALOG: C40.1, C47.1, C50.1, IC6.1 (B), IC6.4 (B), IC11.1 (B), IC11.4 (B), IC13.6 (C); also elsewhere on the board
PP_P15V0_ANALOG: C75.1, C76.1, IC12.3 (C), IC12.6 (C), R46.2; also elsewhere on the board
PULLDN_SENSE_R_CONN: R23.1, X1.1
SMPS_USB_VDD: C113.1, D4.3 (C), D5.3 (C), RLY1.3 (PIN3), RLY2.3 (PIN3); also elsewhere on the board
SPAD_PULLDN_SENSE: IC6.3 (C), R23.2; also elsewhere on the board
STEERING_CASC: IC11.2 (E), IC13.3 (C)
V_IVTEST: RLY2.5 (PIN5), X7.1
V_SCOPE: R35.2, TP9.SIG (1)
V_SPAD: D3.C, RLY1.5 (PIN5), RLY2.10 (PIN10), X4.1

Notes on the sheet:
OUTPUT DRIVER
3.0
1 of 1
